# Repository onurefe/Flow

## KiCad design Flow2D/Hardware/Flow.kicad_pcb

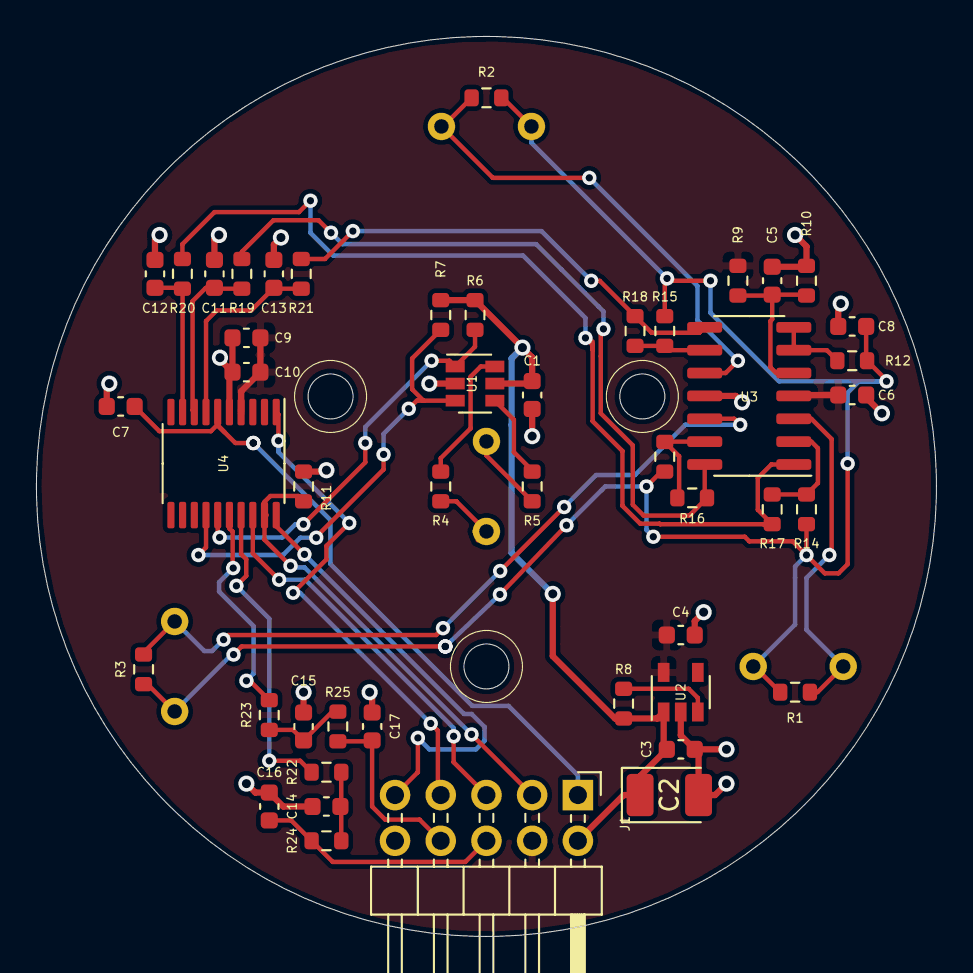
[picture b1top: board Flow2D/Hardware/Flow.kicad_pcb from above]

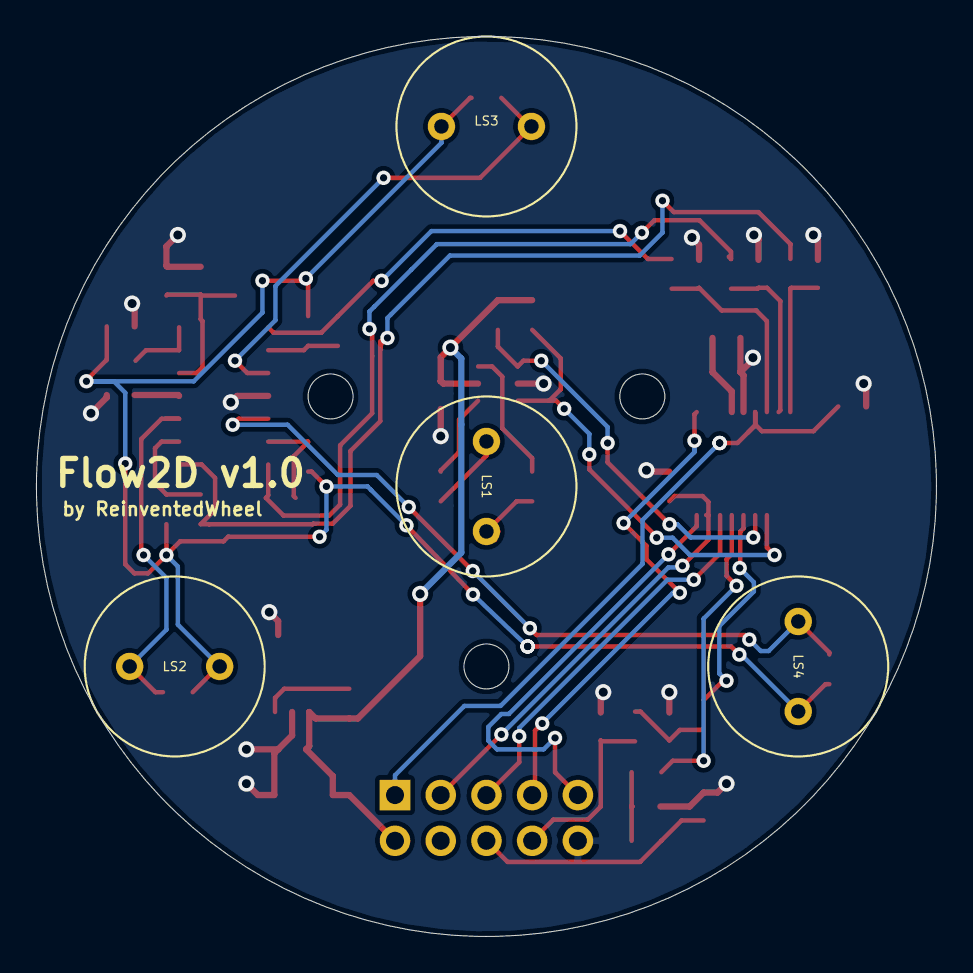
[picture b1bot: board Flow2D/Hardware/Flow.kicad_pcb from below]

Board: 2 copper layers, 50.0 x 50.0 mm, 51 parts (4 on the bottom side), 36 nets.

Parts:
C1, C3, C6, C7, C10, C11, C12, C13: 100n; C_0603_1608Metric
C2: 47u 10v; CP_EIA-3528-21_Kemet-B_Pad1.50x2.35mm_HandSolder
C4, C5, C16, C17: 1u; C_0603_1608Metric
C8, C9, C14, C15: 10u; C_0603_1608Metric
J1: Conn_02x05_Odd_Even; PinHeader_2x05_P2.54mm_Horizontal
LS1, LS2, LS3, LS4: Speaker_Ultrasound; GU1007C-40TR
R1, R2, R3, R8, R9, R10, R11, R16, R17, R18, R24, R25: 12k; R_0603_1608Metric
R4, R5, R12, R19, R20, R21: 18R; R_0603_1608Metric
R6, R7, R13, R14, R15, R22, R23: 1k; R_0603_1608Metric
U1: SN74LVC2G17; SOT-23-6
U2: LR9102G; SOT-23-5
U3: TLV9064IDR; SOIC-14_3.9x8.7mm_P1.27mm
U4: STM32G030F6Px; TSSOP-20_4.4x6.5mm_P0.65mm

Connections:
+5V: C1.1, C2.1, C3.1, J1.2, R6.1, R7.1, R8.2, U1.5, U2.1
/CHA_A: C13.1, R21.1, U4.7
/CHA_B: C11.1, R19.1, U4.8
/CHA_C: C12.1, R20.1, U4.9
/NRST: C7.1, J1.1, U4.6
/OUT_X: C16.1, J1.6, R24.1
/OUT_Y: C17.1, J1.8, R25.1
/PULSE: R6.2, U1.1, U4.15
/PULSE_N: R7.2, U1.3, U4.14
/PWM_X: R22.2, U4.17
/PWM_Y: R23.2, U4.16
/SIGNAL_A: LS3.2, R2.1, U3.10
/SIGNAL_B: LS4.2, R3.1, U3.12
/SIGNAL_C: LS2.2, R1.1, U3.3
/SWCLK: J1.3, R11.1, U4.19
/SWDIO: J1.5, U4.18
/USART_RX: J1.7, U4.1
/USART_TX: J1.9, U4.20
/VGND: C8.1, LS2.1, LS3.1, LS4.1, R1.2, R2.2, R3.2, R12.1, R13.2, R14.2, R15.2
GND: C1.2, C2.2, C3.2, C4.1, C5.2, C6.1, C7.2, C8.2, C9.1, C10.2, C11.2, C12.2, C13.2, C14.1, C15.1, C16.2, C17.2, J1.10, R10.2, R11.2, U1.2, U2.2, U3.11, U4.5
unnamed: C5.1, R9.2, R10.1, U3.5
unnamed: C14.2, R22.1, R24.2
unnamed: C15.2, R23.1, R25.2
unnamed: LS1.1, R4.2
unnamed: LS1.2, R5.2
unnamed: R4.1, U1.6
unnamed: R5.1, U1.4
unnamed: R8.1, U2.3
unnamed: R12.2, U3.6, U3.7
unnamed: R13.1, R16.1, U3.13
unnamed: R14.1, R17.1, U3.2
unnamed: R15.1, R18.1, U3.9
unnamed: R16.2, R19.2, U3.14
unnamed: R17.2, R20.2, U3.1
unnamed: R18.2, R21.2, U3.8
VDD: C4.2, C6.2, C9.2, C10.1, J1.4, R9.1, U2.5, U3.4, U4.4

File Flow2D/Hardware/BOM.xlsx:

Comment | Designator | Footprint | Link | Qty
47u 10v | C2 | CP_EIA-3528-21_Kemet-B_Pad1.50x2.35mm_HandSolder | https://ozdisan.com/passive-components/capacitors/tantalum-c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 | 1
1u | C4, C5, C16, C17 | C_0603_1608Metric | https://ozdisan.com/passive-components/capacitors/smt-smd-an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 | 4
100n | C1, C3, C6, C7, C10, C11, C12, C13 | C_0603_1608Metric | https://ozdisan.com/passive-components/capacitors/smt-smd-an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 | 8
10u | C8, C9, C14, C15 | C_0603_1608Metric | https://ozdisan.com/passive-components/capacitors/smt-smd-an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 | 4
Conn_02x05_Odd_Even | J1 |  | https://ozdisan.com/connectors-and-interconnects/headers/pin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 | 1
Speaker_Ultrasound | LS1, LS2, LS3, LS4
1k | R6, R7, R13, R14, R15, R22, R23 | R_0603_1608Metric | https://ozdisan.com/passive-components/resistors/smt-smd-and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 | 7
18R | R4, R5, R12, R19, R20, R21 | R_0603_1608Metric | https://ozdisan.com/passive-components/resistors/smt-smd-and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 | 6
10k | R1, R2, R3, R8, R9, R10, R11, R16, R17, R18, R24, R25 | R_0603_1608Metric | https://ozdisan.com/passive-components/resistors/smt-smd-and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 | 12
SN74LVC2G17 | U1 | SOT-23-6 | https://ozdisan.com/Product/Detail/461876/SN74LVC2G17DBV | 1
LR9102G | U2 | SOT-23-5 | https://ozdisan.com/integrated-circuits-ics/power-management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 | 1
MCP6024 | U3 | SOIC-14_3.9x8.7mm_P1.27mm | https://ozdisan.com/integrated-circuits-ics/linear-ics/ampli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 | 1
STM32G030F6Px | U4 | TSSOP-20_4.4x6.5mm_P0.65mm | C529330

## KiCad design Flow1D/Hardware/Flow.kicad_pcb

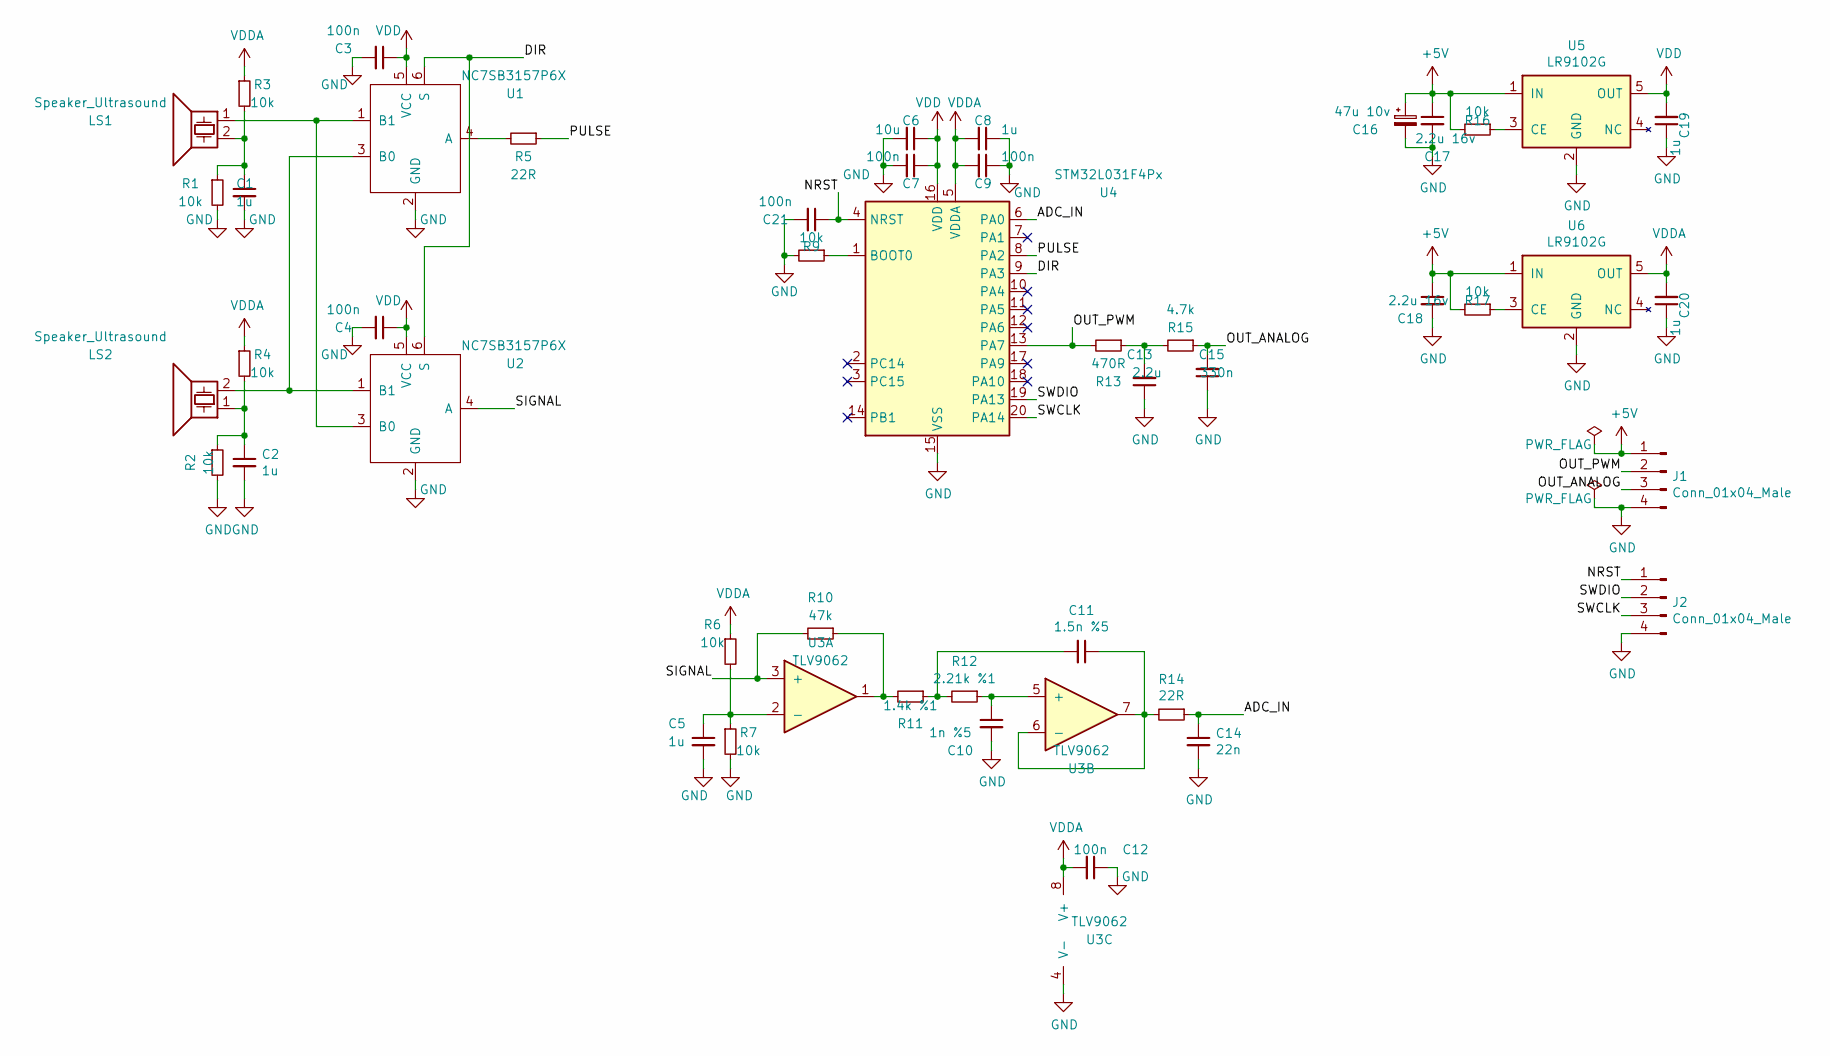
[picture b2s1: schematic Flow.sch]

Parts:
C1, C2, C5, C8, C19, C20: 1u; C_0603_1608Metric
C3, C4, C7, C9, C12, C21: 100n; C_0603_1608Metric
C6: 10u; C_0603_1608Metric
C10: 1n %5; C_0805_2012Metric
C11: 1.5n %5; C_0805_2012Metric
C13: 2.2u; C_0603_1608Metric
C14: 22n; C_0603_1608Metric
C15: 330n; C_0603_1608Metric
C16: 47u 10v; CP_EIA-3528-12_Kemet-T_Pad1.50x2.35mm_HandSolder
C17, C18: 2.2u 16v; C_0603_1608Metric
J1: Conn_01x04_Male; PinHeader_1x04_P2.54mm_Vertical
J2: Conn_01x04_Male; PinHeader_1x04_P1.27mm_Vertical
LS1, LS2: Speaker_Ultrasound; US_RXTX_10mm
R1, R2, R3, R4, R6, R7, R9, R16, R17: 10k; R_0603_1608Metric
R5, R14: 22R; R_0603_1608Metric
R10: 47k; R_0603_1608Metric
R11: 1.4k %1; R_0603_1608Metric
R12: 2.21k %1; R_0603_1608Metric
R13: 470R; R_0603_1608Metric
R15: 4.7k; R_0603_1608Metric
U1, U2: NC7SB3157P6X; SOT-363_SC-70-6_Handsoldering
U3: TLV9062; SOIC-8_3.9x4.9mm_P1.27mm
U4: STM32L031F4Px; TSSOP-20_4.4x6.5mm_P0.65mm
U5, U6: LR9102G; SOT-23-5_HandSoldering

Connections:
+5V: C16.1, C17.1, C18.1, J1.1, R16.2, R17.2, U5.1 (IN), U6.1 (IN)
/ADC_IN: C14.1, R14.1, U4.6 (PA0)
/DIR: U1.6 (S), U2.6 (S), U4.9 (PA3)
/NRST: C21.1, J2.1, U4.4 (NRST)
/OUT_ANALOG: C15.2, J1.3, R15.1
/OUT_PWM: J1.2, R13.2, U4.13 (PA7)
/PULSE: R5.1, U4.8 (PA2)
/SIGNAL: R10.2, U2.4 (A), U3.3 (+)
/SWCLK: J2.3, U4.20 (PA14)
/SWDIO: J2.2, U4.19 (PA13)
GND: C1.2, C2.2, C3.2, C4.2, C5.2, C6.2, C7.2, C8.1, C9.1, C10.2, C12.1, C13.1, C14.2, C15.1, C16.2, C17.2, C18.2, C19.1, C20.1, C21.2, J1.4, J2.4, R1.2, R2.2, R7.2, R9.2, U1.2 (GND), U2.2 (GND), U3.4 (V-), U4.15 (VSS), U5.2 (GND), U6.2 (GND)
unnamed: C1.1, LS1.2, R1.1, R3.2
unnamed: C2.1, LS2.1, R2.1, R4.2
unnamed: C5.1, R6.2, R7.1, U3.2 (-)
unnamed: C10.1, R12.1, U3.5 (+)
unnamed: C11.1, R14.2, U3.6 (-), U3.7
unnamed: C11.2, R11.1, R12.2
unnamed: C13.2, R13.1, R15.2
unnamed: LS1.1, U1.1 (B1), U2.3 (B0)
unnamed: LS2.2, U1.3 (B0), U2.1 (B1)
unnamed: R5.2, U1.4 (A)
unnamed: R9.1, U4.1 (BOOT0)
unnamed: R10.1, R11.2, U3.1
unnamed: R16.1, U5.3 (CE)
unnamed: R17.1, U6.3 (CE)
VDD: C3.1, C4.1, C6.1, C7.1, C19.2, U1.5 (VCC), U2.5 (VCC), U4.16 (VDD), U5.5 (OUT)
VDDA: C8.2, C9.2, C12.2, C20.2, R3.1, R4.1, R6.1, U3.8 (V+), U4.5 (VDDA), U6.5 (OUT)

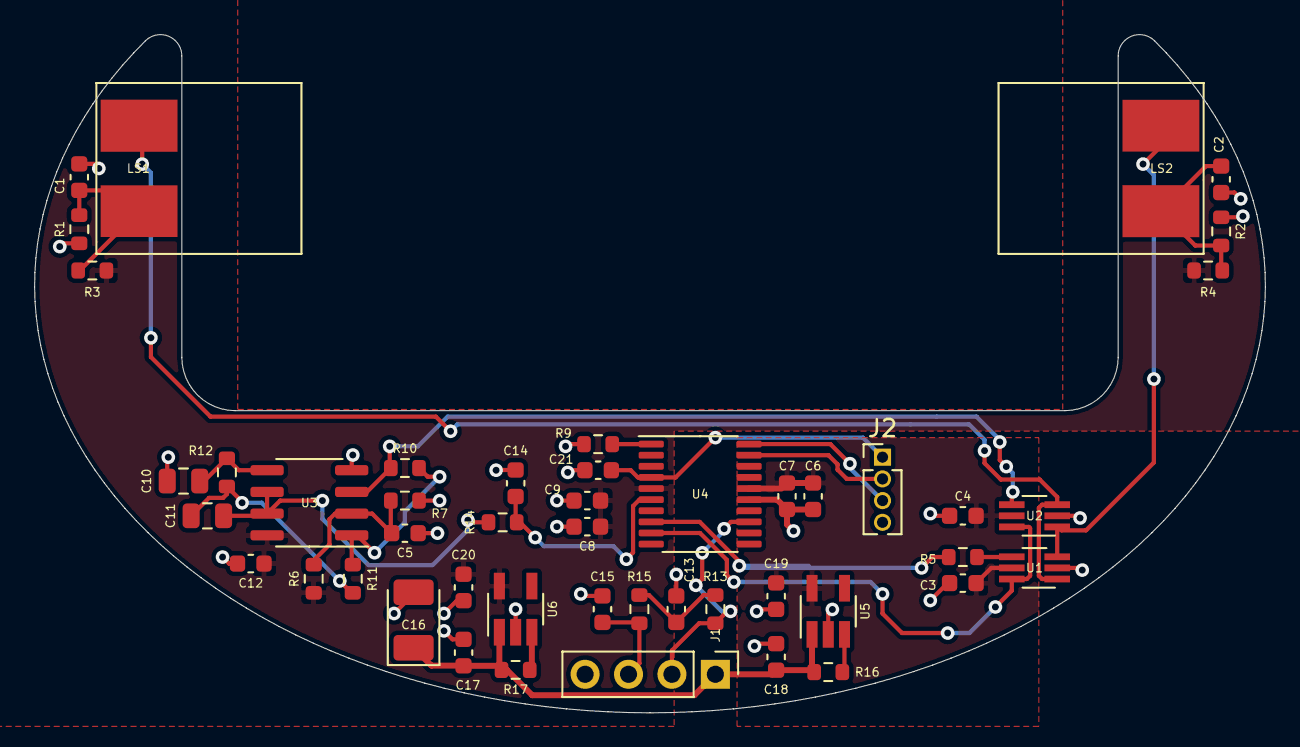
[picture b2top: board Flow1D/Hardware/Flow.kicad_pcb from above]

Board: 2 copper layers, 72.0 x 39.7 mm, 47 parts (0 on the bottom side), 27 nets.

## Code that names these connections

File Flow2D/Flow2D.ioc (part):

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Mcu.Name=STM32G030F6Px
Mcu.Package=TSSOP20
Mcu.UserName=STM32G030F6Px
PA0.GPIOParameters=GPIO_Label
PA0.GPIO_Label=CHA_A
PA0.Mode=IN0
PA0.Signal=ADC1_IN0
PA1.GPIOParameters=GPIO_Label
PA1.GPIO_Label=CHA_B
PA1.Mode=IN1
PA1.Signal=ADC1_IN1
PA10\ [PA12].GPIOParameters=GPIO_Label
PA10\ [PA12].GPIO_Label=PWM_X
PA10\ [PA12].Signal=S_TIM1_CH3
PA13.Mode=Serial_Wire
PA13.Signal=SYS_SWDIO
PA14-BOOT0.Mode=Serial_Wire
PA14-BOOT0.Signal=SYS_SWCLK
PA2.GPIOParameters=GPIO_Label
PA2.GPIO_Label=CHA_C
PA2.Mode=IN2
PA2.Signal=ADC1_IN2
PA6.Signal=S_TIM3_CH1
PA7.GPIOParameters=GPIO_Label
PA7.GPIO_Label=PULSE_N
PA7.Mode=PWM Generation1 CH1 CH1N
PA7.Signal=TIM1_CH1N
PA8.GPIOParameters=GPIO_Label
PA8.GPIO_Label=PULSE
PA8.Signal=S_TIM1_CH1
PA9\ [PA11].GPIOParameters=GPIO_Label
PA9\ [PA11].GPIO_Label=PWM_Y
PA9\ [PA11].Signal=S_TIM1_CH2
PB6.GPIOParameters=GPIO_Label
PB6.GPIO_Label=USART_TX
PB6.Mode=Asynchronous
PB6.Signal=USART1_TX
PB7.GPIOParameters=GPIO_Label
PB7.GPIO_Label=USART_RX
PB7.Mode=Asynchronous
PB7.Signal=USART1_RX
RCC.HSE_VALUE=8000000
RCC.SYSCLKFreq_VALUE=16000000
board=custom

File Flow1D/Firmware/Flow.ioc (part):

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Mcu.Name=STM32L031F(4-6)Px
Mcu.Package=TSSOP20
Mcu.UserName=STM32L031F4Px
PA0-CK_IN.GPIOParameters=GPIO_Label
PA0-CK_IN.GPIO_Label=ADC_IN
PA0-CK_IN.Mode=IN0
PA0-CK_IN.Signal=ADC_IN0
PA13.Mode=Serial_Wire
PA13.Signal=SYS_SWDIO
PA14.Mode=Serial_Wire
PA14.Signal=SYS_SWCLK
PA2.GPIOParameters=GPIO_ModeDefaultPP,GPIO_Speed,GPIO_Label
PA2.GPIO_Label=PULSE
PA2.GPIO_ModeDefaultPP=GPIO_MODE_AF_PP
PA2.GPIO_Speed=GPIO_SPEED_FREQ_MEDIUM
PA2.Signal=S_TIM2_CH3
PA3.GPIOParameters=GPIO_Speed,GPIO_Label,GPIO_ModeDefaultOutputPP
PA3.GPIO_Label=DIR
PA3.GPIO_ModeDefaultOutputPP=GPIO_MODE_OUTPUT_PP
PA3.GPIO_Speed=GPIO_SPEED_FREQ_MEDIUM
PA3.Signal=GPIO_Output
PA7.GPIOParameters=GPIO_Speed,GPIO_Label
PA7.GPIO_Label=ANOUT_PWM
PA7.GPIO_Speed=GPIO_SPEED_FREQ_MEDIUM
PA7.Signal=S_TIM22_CH2
RCC.HSE_VALUE=8000000
RCC.SYSCLKFreq_VALUE=32000000
RCC.SYSCLKSource=RCC_SYSCLKSOURCE_PLLCLK
board=custom

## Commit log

2021-05-09 Flow1D v1.0 hardware completed. Firmware work needed.
    TO DO: Port old firmware to the new platform and library(LL->HAL and STM32F031->STM32L031).
    TO DO: Improve measurement algorithm.
2021-05-31 Backbone of the firmware created.
    +Flow source code needs testing.
    +Theoretical background needs additional verification.
2021-06-04 Test cases for the demodulator code added.
    +Test code added.
    +Demodulator sine table added.
2021-06-05 Demodulator unit works!
    +Demodulator unit added as a test project and tested. Works perfect.
2021-06-06 Test case for the whole speed extraction algorithm.
    +Project works in test case environment. Now it's needed to base it on hardware.
    +Simplification of demodulation algorithm.
2021-07-10 Firmware written, but not tested.
2021-07-13 Working firmware. Prototype v1.0
    +Hardware modifications. Addition of parallel resistors to the transceiver pair.
    +Compensation phasor added.
    +Peripheral configuration problems resolved.
    +Cutoff frequency of the output filter decreased to like 15Hz.
    TODO: Calibration can be added. This way; we needed to add compensation manually. What leads to the mismatch?
2021-09-18 Flow2D fabrication files added.
    Unfortunately schematic file is lost.
2021-09-24 Hardware files of Flow2D found.
2021-09-26 Multiple frequency code base is written.
    TODO:
    +Test on hardware.
    +Implement a measurement algorithm.
    +Output using PWM's.
2021-10-07 Problems related to firmware are solved.
    TODO:
    +Signal level is too low; like 200mV. Need to be increased.
    +Need to be tested with a plastic ring.
    +Piezodriver units response is unknown, need to be determined.
    +A bit more calculation about vectors required.
    +No need for making DMA of the TIM1 active, could be deactivated.
2022-01-21 Works well seemingly!
    TODO: Zero point drift need to be solved.
    TODO: UART communication firmware needed to be added.
2022-02-14 Phase tracking and searching algorithm added.
2022-07-05 Added v2 schematic. Main idea is to correct for transducer shifts.
